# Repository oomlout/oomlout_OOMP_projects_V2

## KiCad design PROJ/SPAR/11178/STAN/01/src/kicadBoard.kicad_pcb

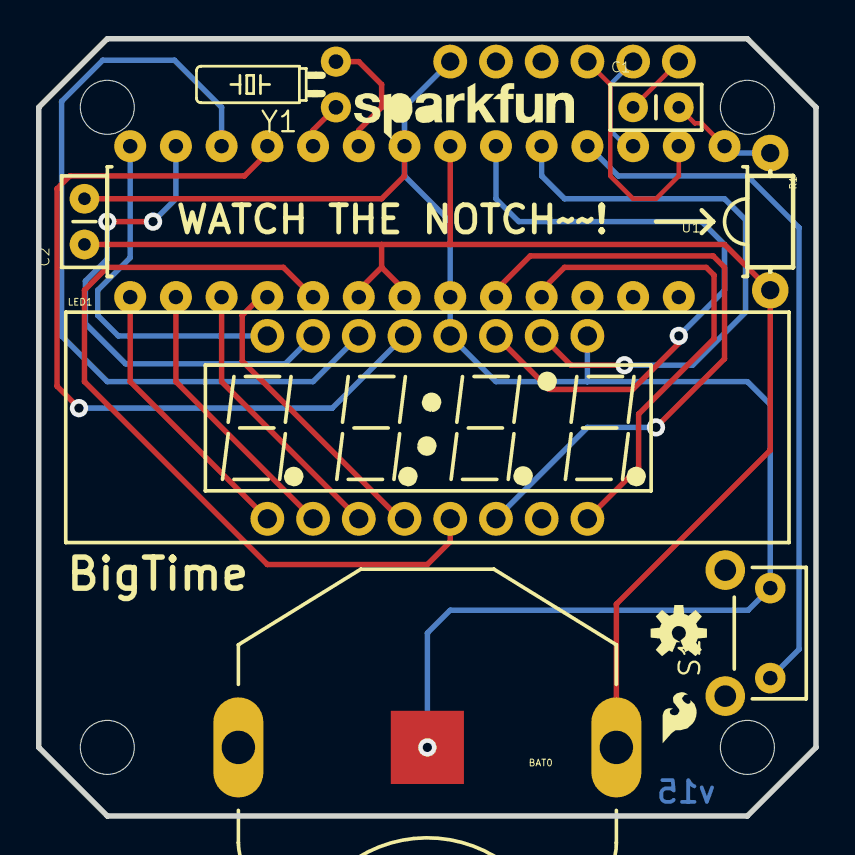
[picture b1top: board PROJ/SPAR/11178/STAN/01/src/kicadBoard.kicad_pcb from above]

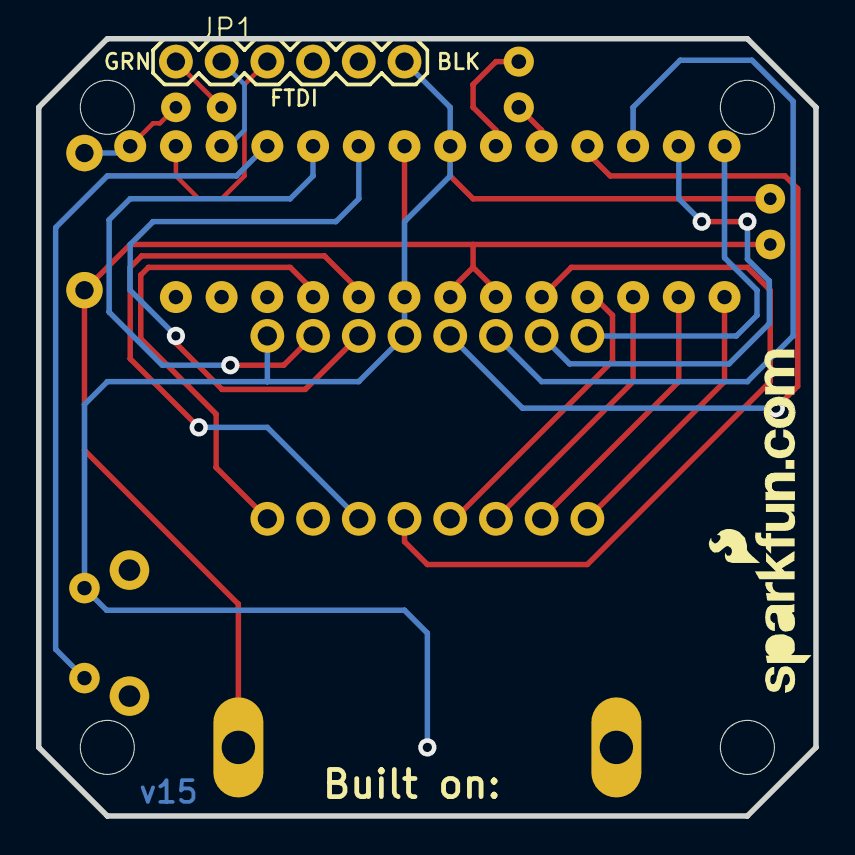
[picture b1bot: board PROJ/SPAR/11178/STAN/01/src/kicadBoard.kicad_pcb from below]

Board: 4 copper layers, 43.2 x 43.2 mm, 18 parts (2 on the bottom side), 22 nets.

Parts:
@HOLE0, @HOLE1, @HOLE2, @HOLE3: (no value)
BAT0: BATTERY_20MM_PTH_COMPACT
C1, C2: 100nF; CAP-PTH-SMALLEZ
JP1: FTDI_BASICPTH; FTDI_BASIC
LED1: 7-SEGMENT-4DIGIT-YOUNGSUNKIT; 7-SEGMENT-4DIGIT-YOUNGSUN-KIT
R1: 100k; AXIAL-0.3-KIT
S1: BUTTON; TACTILE-PTH-SIDEEZ
U1: ATMEGA328P_PDIP_EZ; DIL28-EZ
U$1: LOGO-SFESK; SFE-LOGO-FLAME
U$2: CREATIVE_COMMONS
U$3: LOGO-SFENEW; SFE-NEW-WEBLOGO
U$4: OSHW-LOGOS; OSHW-LOGO-S
U$5: LOGO-SFENW2; SFE-NEW-WEB
Y1: 32.768kHz; TC26HEZ

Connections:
A: LED1.14, U1.12
AMPM: LED1.10, U1.5
B: LED1.16, U1.14
BTN: S1.1, U1.4
C: LED1.13, U1.11
COL: LED1.4, U1.18
D: LED1.3, U1.17
DIG1: LED1.1, U1.15
DIG2: LED1.2, U1.16
DIG3: LED1.6, U1.23
DIG4: LED1.8, U1.24
E: LED1.5, U1.19
F: LED1.11, U1.6
G: LED1.15, U1.13
GND: BAT0.2, C2.2, JP1.GND, LED1.9, LED1.12, S1.2, U1.8, U1.22
unnamed: U1.10, Y1.1
unnamed: U1.9, Y1.2
unnamed: C1.1, JP1.DTR
RST: C1.2, R1.P$1, U1.1
RXI: JP1.TXO, U1.2
TXO: JP1.RXI, U1.3
VCC: BAT0.1, C2.1, R1.P$2, U1.7, U1.20, U1.21

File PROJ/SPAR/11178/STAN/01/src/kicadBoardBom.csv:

"Id";"Designator";"Package";"Quantity";"Designation";"Supplier and ref";
1;"U$1";"SFE-LOGO-FLAME";1;"LOGO-SFESK";;;
2;"U1";"DIL28-EZ";1;"ATMEGA328P_PDIP_EZ";;;
3;"@HOLE1,@HOLE2,@HOLE3,@HOLE0";"";4;"";;;
4;"C2,C1";"CAP-PTH-SMALLEZ";2;"100nF";;;
5;"Y1";"TC26HEZ";1;"32.768kHz";;;
6;"U$5";"SFE-NEW-WEB";1;"LOGO-SFENW2";;;
7;"R1";"AXIAL-0.3-KIT";1;"100k";;;
8;"U$4";"OSHW-LOGO-S";1;"OSHW-LOGOS";;;
9;"BAT0";"BATTERY_20MM_PTH_COMPACT";1;"";;;
10;"U$2";"CREATIVE_COMMONS";1;"CREATIVE_COMMONS";;;
11;"LED1";"7-SEGMENT-4DIGIT-YOUNGSUN-KIT";1;"7-SEGMENT-4DIGIT-YOUNGSUNKIT";;;
12;"S1";"TACTILE-PTH-SIDEEZ";1;"BUTTON";;;
13;"U$3";"SFE-NEW-WEBLOGO";1;"LOGO-SFENEW";;;
14;"JP1";"FTDI_BASIC";1;"FTDI_BASICPTH";;;

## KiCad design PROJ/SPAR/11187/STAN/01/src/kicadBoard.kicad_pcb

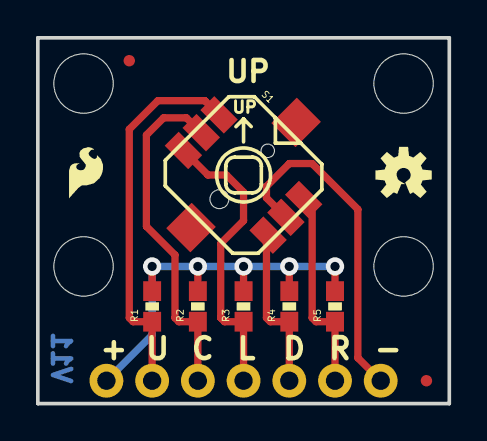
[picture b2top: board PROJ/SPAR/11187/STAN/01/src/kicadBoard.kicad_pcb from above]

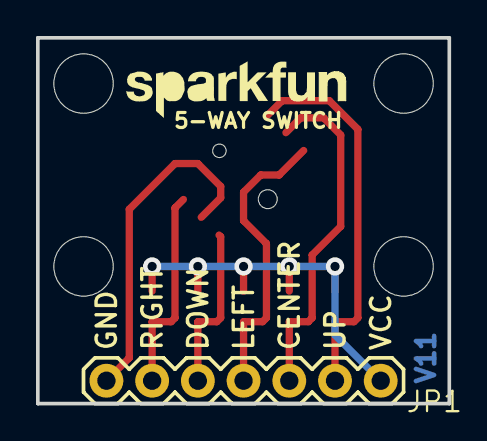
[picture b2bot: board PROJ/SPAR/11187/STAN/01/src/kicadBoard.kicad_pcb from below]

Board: 2 copper layers, 22.9 x 20.3 mm, 17 parts (2 on the bottom side), 7 nets.

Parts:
JP1: 1X07
JP2, JP7: FIDUCIALUFIDUCIAL; MICRO-FIDUCIAL
JP3, JP4, JP5, JP6: STAND-OFF
JP9: LOGO-SFESK; SFE-LOGO-FLAME
JP10: LOGO-SFENW2; SFE-NEW-WEB
R1, R2, R3, R4, R5: 10K; 0603-RES
S1: 5-WAY-TACTILE-SWITCH; JOYSTICK_MINI
U$1: OSHW-LOGOS; OSHW-LOGO-S
U$2: CREATIVE_COMMONS

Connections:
CENTER: JP1.3, R2.1, S1.CTR
DOWN: JP1.5, R4.1, S1.D
GND: JP1.7, S1.GND
LEFT: JP1.4, R3.1, S1.C
RIGHT: JP1.6, R5.1, S1.B
UP: JP1.2, R1.1, S1.A
VCC: JP1.1, R1.2, R2.2, R3.2, R4.2, R5.2

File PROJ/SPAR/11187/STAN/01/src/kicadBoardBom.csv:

"Id";"Designator";"Package";"Quantity";"Designation";"Supplier and ref";
1;"JP2,JP7";"MICRO-FIDUCIAL";2;"FIDUCIALUFIDUCIAL";;;
2;"JP6,JP5,JP3,JP4";"STAND-OFF";4;"STAND-OFF";;;
3;"S1";"JOYSTICK_MINI";1;"5-WAY-TACTILE-SWITCH";;;
4;"R3,R2,R1,R4,R5";"0603-RES";5;"10K";;;
5;"U$2";"CREATIVE_COMMONS";1;"CREATIVE_COMMONS";;;
6;"JP9";"SFE-LOGO-FLAME";1;"LOGO-SFESK";;;
7;"U$1";"OSHW-LOGO-S";1;"OSHW-LOGOS";;;
8;"JP1";"1X07";1;"";;;
9;"JP10";"SFE-NEW-WEB";1;"LOGO-SFENW2";;;

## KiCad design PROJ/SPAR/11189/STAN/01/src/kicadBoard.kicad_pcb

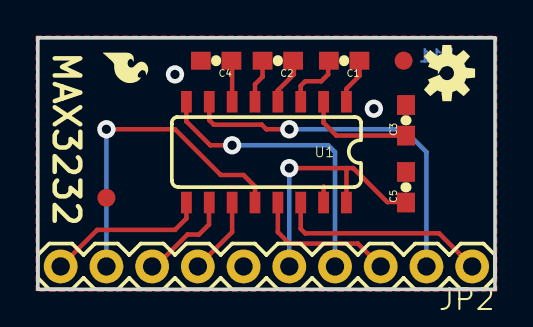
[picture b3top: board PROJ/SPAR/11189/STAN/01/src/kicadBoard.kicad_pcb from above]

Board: 2 copper layers, 25.4 x 14.0 mm, 12 parts (0 on the bottom side), 16 nets.

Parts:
C1, C2, C3, C4, C5: .1uF; 0603-CAP
FID1, FID2: FIDUCIAL1X2; FIDUCIAL-1X2
FRAME1: CREATIVE_COMMONS
JP2: M10"; 1X10
LOGO1: SFE_LOGO_FLAME.1_INCH; SFE_LOGO_FLAME_.1
U1: MAX3232; SO016
U$1: OSHW-LOGOS; OSHW-LOGO-S

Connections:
C1+: C1.1, U1.1
C1-: C1.2, U1.3
C2+: C2.1, U1.4
C2-: C2.2, U1.5
GND: C3.2, C4.2, C5.2, JP2.6, U1.15
R1IN: JP2.3, U1.13
R1OUT: JP2.9, U1.12
R2IN: JP2.4, U1.8
R2OUT: JP2.10, U1.9
T1IN: JP2.7, U1.11
T1OUT: JP2.1, U1.14
T2IN: JP2.8, U1.10
T2OUT: JP2.2, U1.7
V+: C3.1, U1.2
V-: C4.1, U1.6
VCC: C5.1, JP2.5, U1.16

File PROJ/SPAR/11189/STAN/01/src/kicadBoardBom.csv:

"Id";"Designator";"Package";"Quantity";"Designation";"Supplier and ref";
1;"C4,C2,C1,C3,C5";"0603-CAP";5;".1uF";;;
2;"U1";"SO016";1;"MAX3232";;;
3;"LOGO1";"SFE_LOGO_FLAME_.1";1;"SFE_LOGO_FLAME.1_INCH";;;
4;"U$1";"OSHW-LOGO-S";1;"OSHW-LOGOS";;;
5;"FRAME1";"CREATIVE_COMMONS";1;"";;;
6;"FID2,FID1";"FIDUCIAL-1X2";2;"FIDUCIAL1X2";;;
7;"JP2";"1X10";1;"M10"";;;

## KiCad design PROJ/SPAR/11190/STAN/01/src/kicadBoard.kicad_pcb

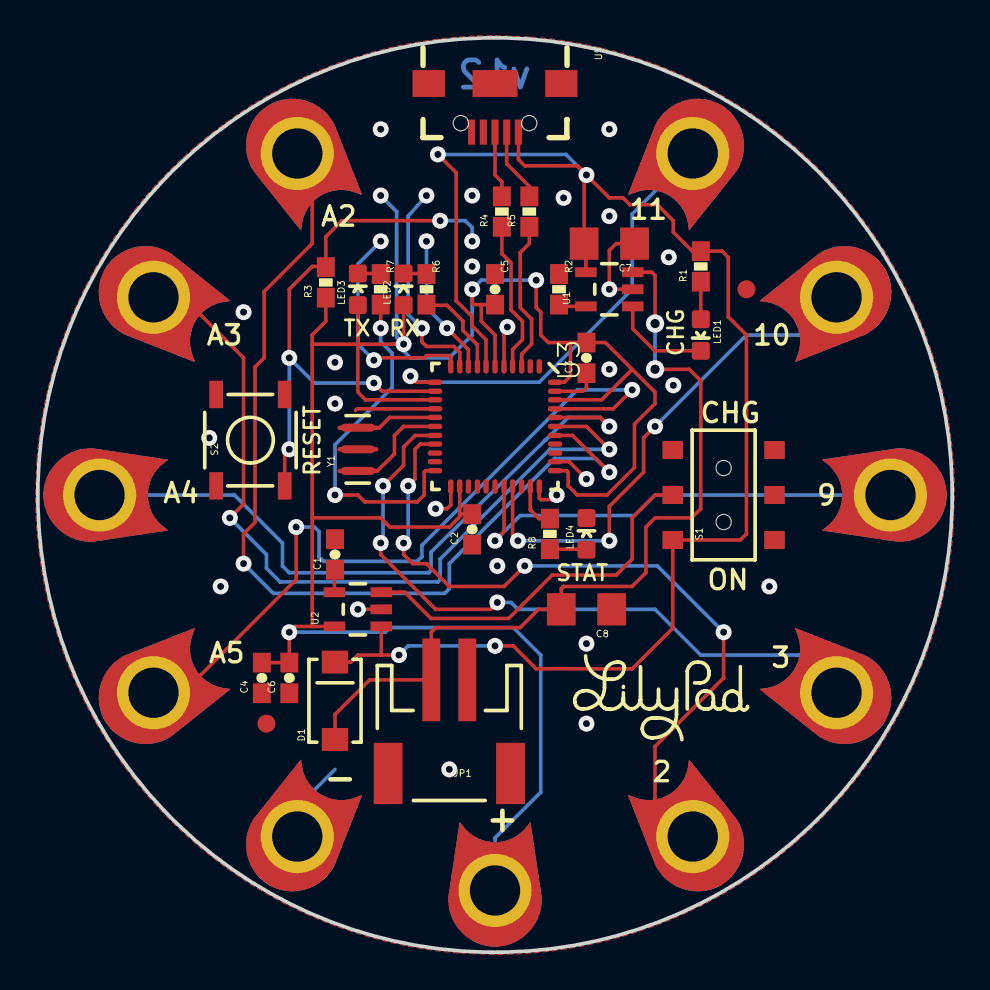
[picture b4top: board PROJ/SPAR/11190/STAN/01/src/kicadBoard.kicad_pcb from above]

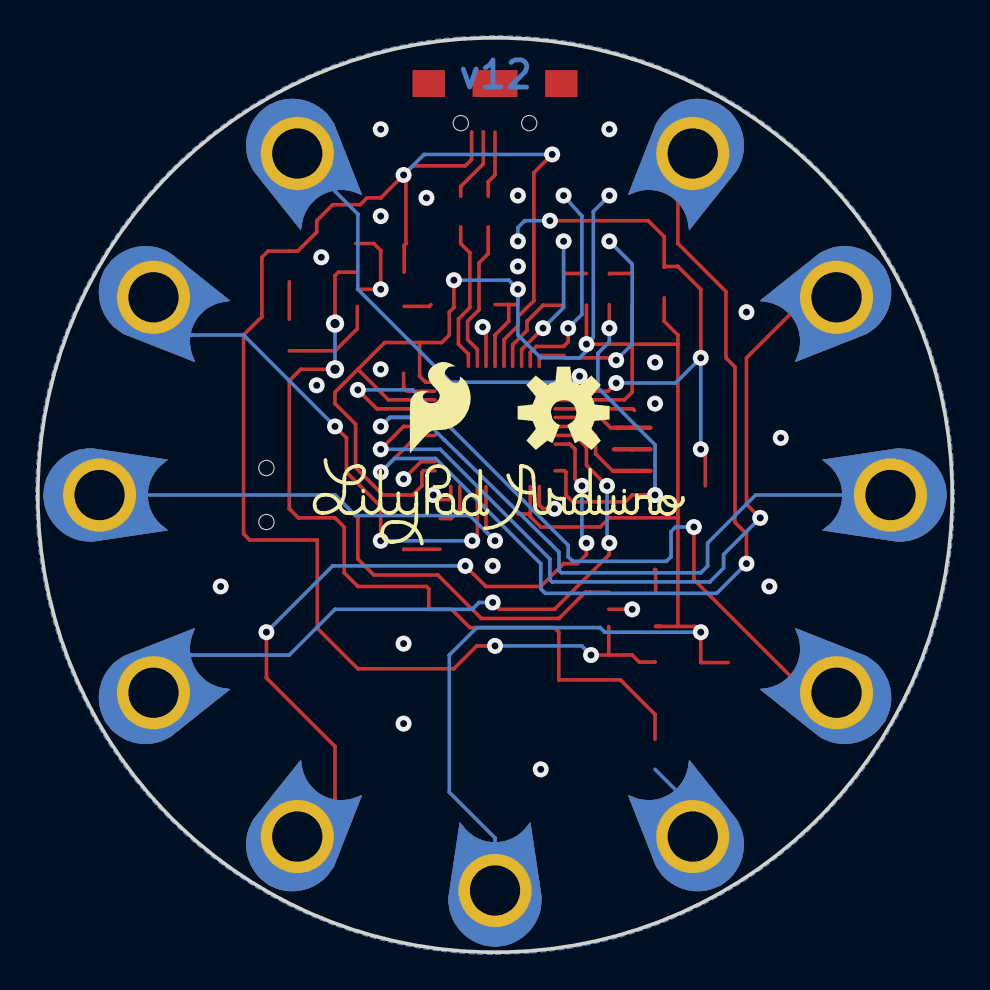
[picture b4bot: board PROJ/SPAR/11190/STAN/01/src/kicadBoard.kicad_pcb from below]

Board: 4 copper layers, 50.8 x 50.8 mm, 47 parts (3 on the bottom side), 31 nets.

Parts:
+0: SEWTAP9; PETAL-LONG-1-2SIDE
-0: SEWTAP9; PETAL-LONG-1-2SIDE
A2, A3, A4, A5: SEWTAP9; PETAL-LONG-1-2SIDE
C1: 470pF; 0603-CAP
C2, C3, C4: .1uF; 0603-CAP
C5: 1uF; 0603-CAP
C6: 4.7uF; 0603-CAP
C7, C8: 4.7uF; 1206
D1: B340A; SMA-DIODE
D5, D6, D9, D10, D11: SEWTAP9; PETAL-LONG-1-2SIDE
FRAME1: FRAME-LETTER; CREATIVE_COMMONS
JP1: JST-2; JST-2-SMD
JP2, JP3: FIDUCIAL1X2; FIDUCIAL-1X2
LED1, LED2, LED3, LED4: RED; LED-0603
R1, R6, R7, R8: 330; 0603-RES
R2, R3: 10k; 0603-RES
R4, R5: 22; 0603-RES
S1: AYZ0202
S2: !RESET; TACTILE_SWITCH_SMD
U1: MCP73831; SOT23-5
U2: MIC5219; SOT23-5
U3: ATMEGA32U41:1-LESS_PASTE; QFN-44-NOPAD_1_1-LESS_PASTE
U5: USB-AB-MICRO-SMD_V03
U$1: LOGO-LPLPA; LOGO-LPA
U$5: OSHW-LOGOM; OSHW-LOGO-M
U$7: SFE_LOGO_FLAME_.2
U$13: LOGO-LPLP; LOGO-LILYPAD
Y1: 8MHz; RESONATOR-SMD

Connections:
3.3V: +0.1, C2.2, C3.2, C4.2, C5.2, C6.2, LED2.A, LED3.A, R3.1, U2.5, U3.6, U3.14, U3.24, U3.34, U3.42, U3.44
5V: C7.2, D1.C, R1.2, S1.1, U1.4, U2.1, U3.7, U5.VBUS1
D+: R4.1, U3.4
D-: R5.1, U3.3
GND: -0.1, C1.2, C2.1, C3.1, C4.1, C5.1, C6.1, C7.1, C8.1, JP1.1, LED4.C, R2.1, S1.3, S2.1, U1.2, U2.2, U3.5, U3.15, U3.23, U3.33, U3.35, U3.43, U5.GND1, Y1.2
unnamed: LED2.C, R6.1
unnamed: S1.2, U2.3
unnamed: LED1.A, R1.1
unnamed: LED1.C, U1.1
unnamed: U3.17, Y1.1
unnamed: R2.2, U1.5
unnamed: U3.16, Y1.3
unnamed: C1.1, U2.4
unnamed: D11.1, U3.12
unnamed: D10.1, U3.30
unnamed: D9.1, U3.29
unnamed: D5.1, U3.19
unnamed: D6.1, U3.18
unnamed: A5.1, U3.41
unnamed: A4.1, U3.40
unnamed: A3.1, U3.39
unnamed: A2.1, U3.38
unnamed: LED4.A, R8.1
unnamed: R5.2, U5.D-1
unnamed: R4.2, U5.D+1
unnamed: LED3.C, R7.1
RESET: R3.2, S2.3, U3.13
RX_LED: R6.2, U3.8
TX_LED: R7.2, U3.22
USER_LED: R8.2, U3.32
V_BATT: C8.2, D1.A, JP1.2, U1.3

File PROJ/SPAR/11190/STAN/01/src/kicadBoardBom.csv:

"Id";"Designator";"Package";"Quantity";"Designation";"Supplier and ref";
1;"-0,D5,A2,D11,D9,A4,A5,D6,D10,A3,+0";"PETAL-LONG-1-2SIDE";11;"SEWTAP9";;;
2;"R8,R6,R7,R1";"0603-RES";4;"330";;;
3;"C8,C7";"1206";2;"4.7uF";;;
4;"S2";"TACTILE_SWITCH_SMD";1;"!RESET";;;
5;"C5";"0603-CAP";1;"1uF";;;
6;"Y1";"RESONATOR-SMD";1;"8MHz";;;
7;"R3,R2";"0603-RES";2;"10k";;;
8;"JP3,JP2";"FIDUCIAL-1X2";2;"FIDUCIAL1X2";;;
9;"LED3,LED2,LED4,LED1";"LED-0603";4;"RED";;;
10;"C4,C3,C2";"0603-CAP";3;".1uF";;;
11;"U$13";"LOGO-LILYPAD";1;"LOGO-LPLP";;;
12;"S1";"AYZ0202";1;"";;;
13;"JP1";"JST-2-SMD";1;"JST-2";;;
14;"FRAME1";"CREATIVE_COMMONS";1;"FRAME-LETTER";;;
15;"C6";"0603-CAP";1;"4.7uF";;;
16;"R5,R4";"0603-RES";2;"22";;;
17;"C1";"0603-CAP";1;"470pF";;;
18;"D1";"SMA-DIODE";1;"B340A";;;
19;"U2";"SOT23-5";1;"MIC5219";;;
20;"U1";"SOT23-5";1;"MCP73831";;;
21;"U3";"QFN-44-NOPAD_1_1-LESS_PASTE";1;"ATMEGA32U41:1-LESS_PASTE";;;
22;"U5";"USB-AB-MICRO-SMD_V03";1;"";;;
23;"U$5";"OSHW-LOGO-M";1;"OSHW-LOGOM";;;
24;"U$7";"SFE_LOGO_FLAME_.2";1;"";;;
25;"U$1";"LOGO-LPA";1;"LOGO-LPLPA";;;

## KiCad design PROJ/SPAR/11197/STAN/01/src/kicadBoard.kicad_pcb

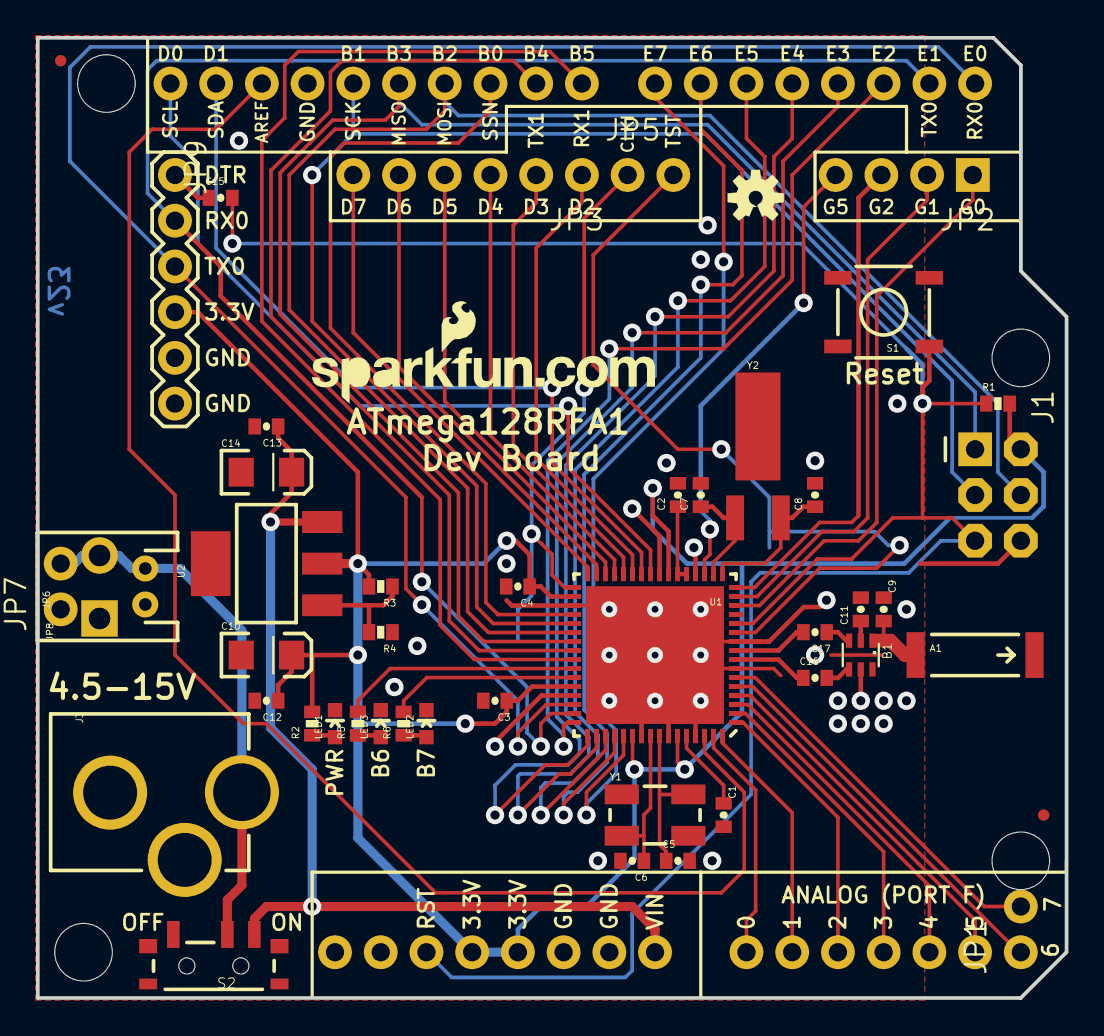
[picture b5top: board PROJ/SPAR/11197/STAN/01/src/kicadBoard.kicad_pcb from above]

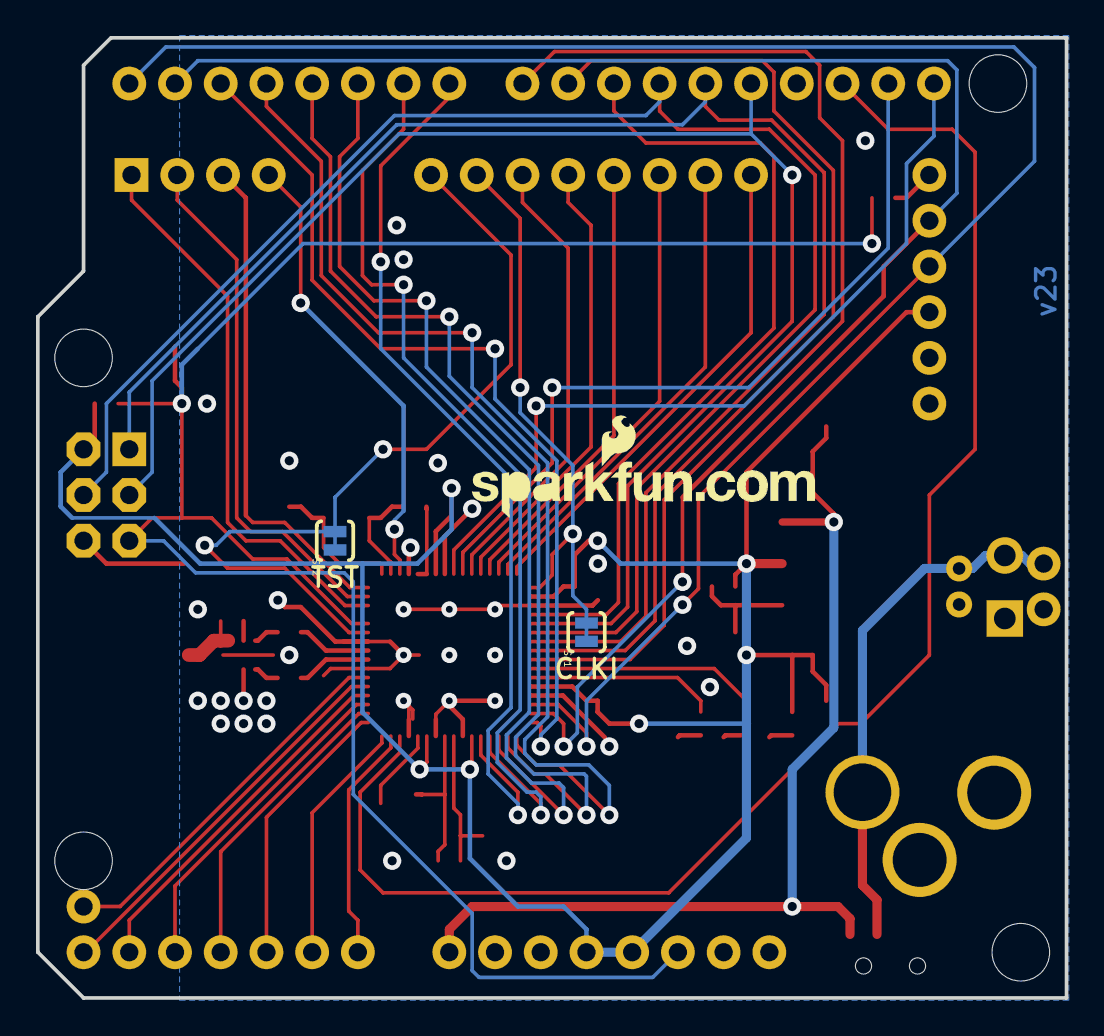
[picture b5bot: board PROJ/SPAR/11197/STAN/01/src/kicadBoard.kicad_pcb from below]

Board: 2 copper layers, 57.1 x 53.3 mm, 52 parts (3 on the bottom side), 61 nets.

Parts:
A1: ANTENNA2SMD5; ANTENNA-CHIP5
B1: 748421245; BALUN
C1, C2, C3, C4, C12: 1uF; 0402-CAP
C5, C6, C7, C8: 12pF; 0402-CAP
C9: 0.75pF; 0402-CAP
C10, C14: 10uF; EIA3216
C11: 22pF; 0402-CAP
C13, C15: 0.1uF; 0402-CAP
C16, C17: JUMP; 0402-CAP
FID1, FID2: FIDUCIALUFIDUCIAL; MICRO-FIDUCIAL
J1: ISP; 2X3-NS
J2: ARDUINO_UNO_R3
J3: POWER_JACKPTH_LOCK; POWER_JACK_PTH_LOCK
JP1, JP5, JP7: 1X02_NO_SILK
JP2: 1X04_NO_SILK
JP3: 1X06_NS
JP4, JP10: LOGO-SFENEW; SFE-NEW-WEBLOGO
JP6: JST-2-PTH
JP8: SCREWTERMINAL-3.5MM-2-NS
JP9: FTDI; FTDI_BASIC
LED1: RED; LED-0603
LED2, LED3: GREEN; LED-0603
R1: 10k; 0402-RES
R2: 1k; 0402-RES
R3: 240; 0402-RES
R4: 390; 0402-RES
R5, R6: 330; 0402-RES
S1: TACTILE_SWITCH_SMD
S2: SWITCH-SPST-SMD-A
SJ1, SJ2: SJ_2S-TRACE
U1: ATMEGA128RFA1; QFN-64
U2: LM1117; SOT223
U$1: OSHW-LOGOS; OSHW-LOGO-S
Y1: 16MHz; CRYSTAL-SMD-5X3
Y2: 32.768kHz; CRYSTAL-32KHZ-SMD

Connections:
3.3V: C3.1, C4.1, C10.A, C12.1, J1.2, J2.3.3V, J2.5V, JP9.VCC, R1.2, R2.2, R3.2, U1.23, U1.34, U1.44, U1.54, U1.59, U2.2
A0: J2.A0, U1.63
A1: J2.A1, U1.64
A2: J2.A2, U1.1
A3: J2.A3, U1.2
A4: J2.A4, U1.3
A5: J2.A5, U1.4
A6: JP1.1, U1.5
A7: JP1.2, U1.6
AREF: J2.AREF, U1.62
AVDD: C1.1, U1.60
CLKI: JP5.1, SJ1.2, U1.33
DTR: C15.1, JP9.DTR
DVDD: C2.1, U1.21, U1.22
FB: R3.1, R4.2, U2.1
GND: B1.5, C1.2, C2.2, C3.2, C4.2, C5.2, C6.2, C7.2, C8.2, C9.1, C10.C, C11.2, C12.2, C13.2, C14.C, J1.6, J2.GND@0, J2.GND@1, J2.GND@2, J3.GND, J3.GNDBREAK, JP6.1, JP7.1, JP8.1, JP9.GND, LED1.C, LED2.C, LED3.C, R4.1, S1.3, SJ1.1, SJ2.1, U1.7, U1.10, U1.20, U1.24, U1.35, U1.45, U1.55, U1.58, U1.61, U1.65
MISO: J1.1, J2.D12, U1.39
MOSI: J1.4, J2.D11, U1.38
unnamed: LED1.A, R2.1
unnamed: C5.1, U1.57, Y1.3
unnamed: C6.1, U1.56, Y1.1
unnamed: C7.1, U1.18, Y2.X1
unnamed: C8.1, U1.17, Y2.X2
unnamed: B1.2, C11.1
unnamed: LED3.A, R5.1
unnamed: J3.PWR, JP6.2, JP7.2, JP8.2, S2.2
unnamed: B1.4, C16.2
unnamed: B1.3, C17.1
unnamed: LED2.A, R6.1
PB4: J2.D9, U1.40
PB5: J2.D8, U1.41
PB6: R5.2, U1.42
PB7: R6.2, U1.43
PD4: JP3.3, U1.29
PD5: JP3.4, U1.30
PD6: JP3.5, U1.31
PD7: JP3.6, U1.32
PE2: J2.D2, U1.48
PE3: J2.D3, U1.49
PE4: J2.D4, U1.50
PE5: J2.D5, U1.51
PE6: J2.D6, U1.52
PE7: J2.D7, U1.53
PG0: JP2.1, U1.14
PG1: JP2.2, U1.15
PG2: JP2.3, U1.16
PG5: JP2.4, U1.19
RESET: C15.2, J1.5, J2.RES, R1.1, S1.1, U1.12
RFANT: A1.FEED, B1.1, C9.2
RFN: C17.2, U1.9
RFP: C16.1, U1.8
RX0: J2.RX, JP9.TXO, U1.46
RX1: JP3.1, U1.27
SCK: J1.3, J2.D13, U1.37
SCL: J2.SCL, U1.25
SDA: J2.SDA, U1.26
SSN: J2.D10, U1.36
TST: JP5.2, SJ2.2, U1.11
TX0: J2.TX, JP9.RXI, U1.47
TX1: JP3.2, U1.28
VCC: C13.1, C14.A, J2.VIN, S2.1, U2.3

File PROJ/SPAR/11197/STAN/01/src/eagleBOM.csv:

"Part";"Value";"Device";"Package";"Description";"";
"A1";"ANTENNA2SMD5";"ANTENNA2SMD5";"ANTENNA-CHIP5";"Chip antenna";"";
"B1";"748421245";"BALUN0805";"BALUN";"0805 footprint balun- Ember 351/357";"";
"C1";"1uF";"CAP0402-CAP";"0402-CAP";"Capacitor";"";
"C2";"1uF";"CAP0402-CAP";"0402-CAP";"Capacitor";"";
"C3";"1uF";"CAP0402-CAP";"0402-CAP";"Capacitor";"";
"C4";"1uF";"CAP0402-CAP";"0402-CAP";"Capacitor";"";
"C5";"12pF";"CAP0402-CAP";"0402-CAP";"Capacitor";"";
"C6";"12pF";"CAP0402-CAP";"0402-CAP";"Capacitor";"";
"C7";"12pF";"CAP0402-CAP";"0402-CAP";"Capacitor";"";
"C8";"12pF";"CAP0402-CAP";"0402-CAP";"Capacitor";"";
"C9";"0.75pF";"CAP0402-CAP";"0402-CAP";"Capacitor";"";
"C10";"10uF";"CAP_POL1206";"EIA3216";"Capacitor Polarized";"";
"C11";"22pF";"CAP0402-CAP";"0402-CAP";"Capacitor";"";
"C12";"1uF";"CAP0402-CAP";"0402-CAP";"Capacitor";"";
"C13";"0.1uF";"CAP0402-CAP";"0402-CAP";"Capacitor";"";
"C14";"10uF";"CAP_POL1206";"EIA3216";"Capacitor Polarized";"";
"C15";"0.1uF";"CAP0402-CAP";"0402-CAP";"Capacitor";"";
"C16";"JUMP";"CAP0402-CAP";"0402-CAP";"Capacitor";"";
"C17";"JUMP";"CAP0402-CAP";"0402-CAP";"Capacitor";"";
"FID1";"FIDUCIALUFIDUCIAL";"FIDUCIALUFIDUCIAL";"MICRO-FIDUCIAL";"Fiducial Alignment Points";"";
"FID2";"FIDUCIALUFIDUCIAL";"FIDUCIALUFIDUCIAL";"MICRO-FIDUCIAL";"Fiducial Alignment Points";"";
"J1";"ISP";"AVR_SPI_PRG_6NS";"2X3-NS";"AVR ISP 6 Pin";"";
"J2";"ARDUINO_UNO_R3";"ARDUINO_UNO_R3";"ARDUINO_UNO_R3";"Arduino Uno R3";"";
"J3";"POWER_JACKPTH_LOCK";"POWER_JACKPTH_LOCK";"POWER_JACK_PTH_LOCK";"Power Jack";"";
"JP1";"";"M021X02_NO_SILK";"1X02_NO_SILK";"Header 2";"";
"JP2";"";"M041X04_NO_SILK";"1X04_NO_SILK";"Header 4";"";
"JP3";"";"M06SIP-NS";"1X06_NS";"Header 6";"";
"JP4";"LOGO-SFENEW";"LOGO-SFENEW";"SFE-NEW-WEBLOGO";"Spark Fun Electronics PCB Logo";"";
"JP5";"";"M021X02_NO_SILK";"1X02_NO_SILK";"Header 2";"";
"JP6";"";"M02JST-PTH-2";"JST-2-PTH";"Header 2";"";
"JP7";"";"M021X02_NO_SILK";"1X02_NO_SILK";"Header 2";"";
"JP8";"";"M023.5MM-NO_SILK";"SCREWTERMINAL-3.5MM-2-NS";"Header 2";"";
"JP9";"FTDI";"FTDI_BASICPTH";"FTDI_BASIC";"FTDI Basic header with labels";"";
"JP10";"LOGO-SFENEW";"LOGO-SFENEW";"SFE-NEW-WEBLOGO";"Spark Fun Electronics PCB Logo";"";
"LED1";"RED";"LED0603";"LED-0603";"LEDs";"";
"LED2";"GREEN";"LED0603";"LED-0603";"LEDs";"";
"LED3";"GREEN";"LED0603";"LED-0603";"LEDs";"";
"R1";"10k";"RESISTOR0402-RES";"0402-RES";"Resistor";"";
"R2";"1k";"RESISTOR0402-RES";"0402-RES";"Resistor";"";
"R3";"240";"RESISTOR0402-RES";"0402-RES";"Resistor";"";
"R4";"390";"RESISTOR0402-RES";"0402-RES";"Resistor";"";
"R5";"330";"RESISTOR0402-RES";"0402-RES";"Resistor";"";
"R6";"330";"RESISTOR0402-RES";"0402-RES";"Resistor";"";
"S1";"";"SWITCH-MOMENTARY-2SMD";"TACTILE_SWITCH_SMD";"Various NO switches- pushbuttons, reed, etc";"";
"S2";"";"SWITCH-SPST-SMD-A";"SWITCH-SPST-SMD-A";"SPST Switch";"";
"SJ1";"";"SOLDERJUMPERTRACE";"SJ_2S-TRACE";"Solder Jumper";"";
"SJ2";"";"SOLDERJUMPERTRACE";"SJ_2S-TRACE";"Solder Jumper";"";
"U$1";"OSHW-LOGOS";"OSHW-LOGOS";"OSHW-LOGO-S";"Open Source Hardware Logo This logo indicates the piece of hardware it is found on incorporates a OSHW license and/or adheres to the definition of open source hardware found here: http://freedomdefined.org/OSHW";"";
"U1";"ATMEGA128RFA1";"ATMEGA128RFA1";"QFN-64";"ATmega128RFA1";"";
"U2";"LM1117";"V_REG_317SMD";"SOT223";"Voltage Regulator";"";
"Y1";"16MHz";"CRYSTAL5X3";"CRYSTAL-SMD-5X3";"Various standard crystals. Proven footprints. Spark Fun Electronics SKU : COM-00534";"";
"Y2";"32.768kHz";"CRYSTAL32-SMD";"CRYSTAL-32KHZ-SMD";"Various standard crystals. Proven footprints. Spark Fun Electronics SKU : COM-00534";"";

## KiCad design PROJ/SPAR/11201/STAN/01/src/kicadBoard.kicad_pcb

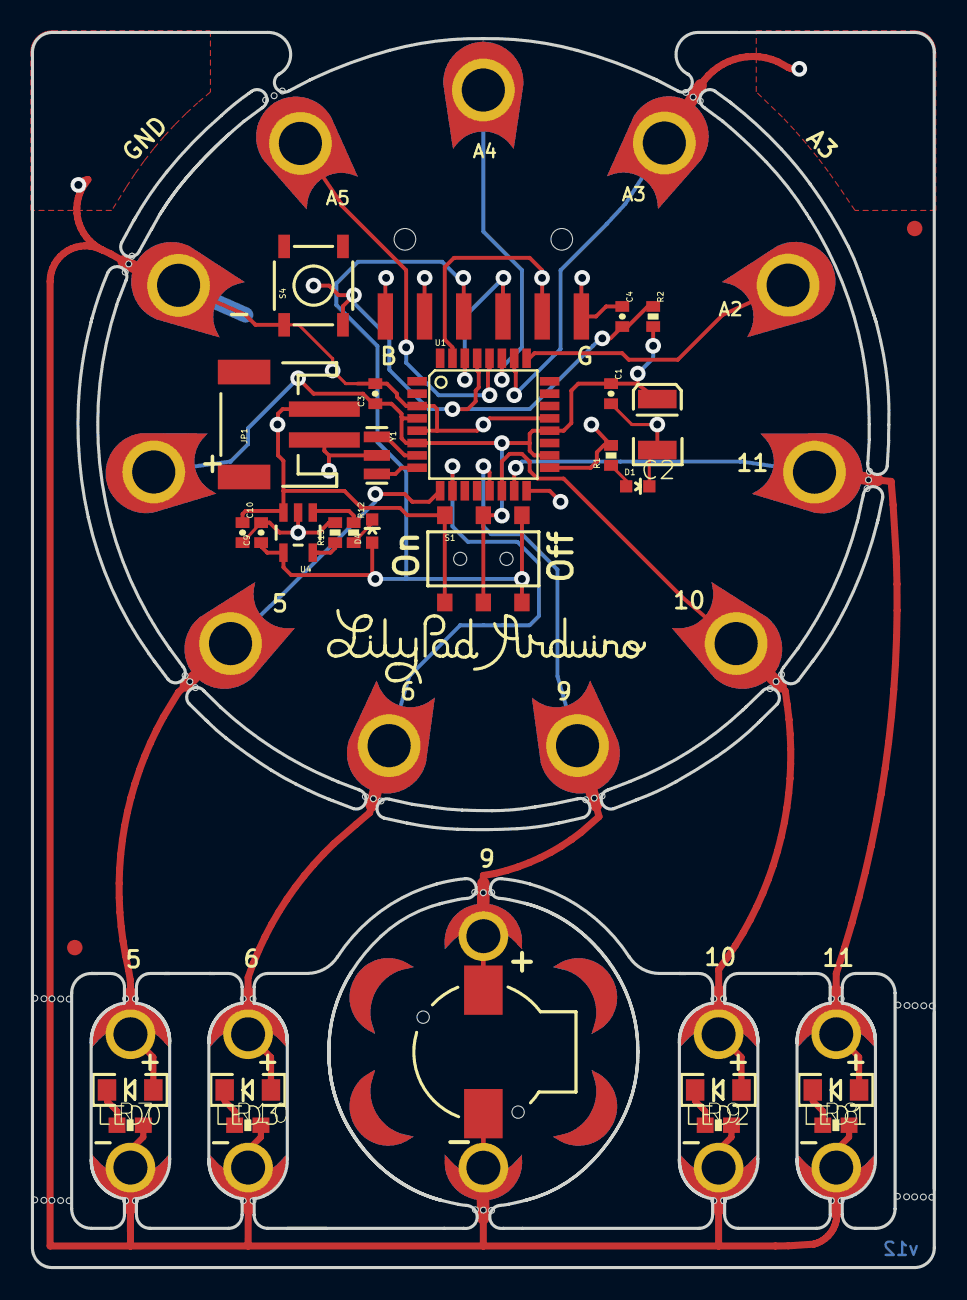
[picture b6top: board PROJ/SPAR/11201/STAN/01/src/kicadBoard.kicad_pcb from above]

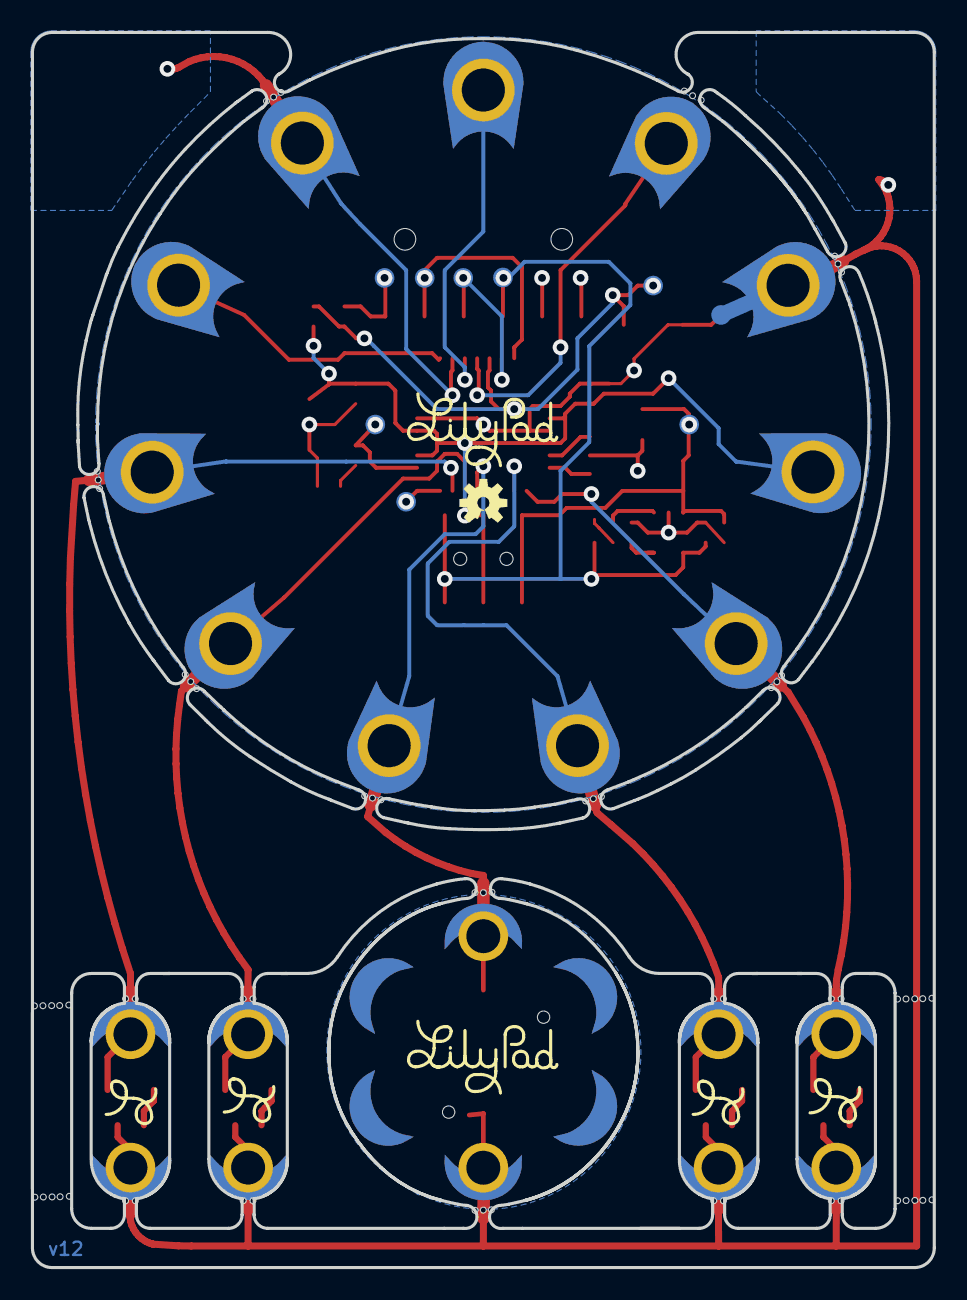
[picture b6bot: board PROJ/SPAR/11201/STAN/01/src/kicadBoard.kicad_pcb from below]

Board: 2 copper layers, 58.4 x 80.0 mm, 139 parts (16 on the bottom side), 29 nets.

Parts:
@HOLE0, @HOLE1, @HOLE2, @HOLE3, @HOLE4, @HOLE5, @HOLE6, @HOLE7, @HOLE8, @HOLE9, @HOLE10, @HOLE11, @HOLE12, @HOLE13, @HOLE14, @HOLE15, @HOLE16, @HOLE17, @HOLE18, @HOLE19, @HOLE20, @HOLE21, @HOLE22, @HOLE23, @HOLE24, @HOLE25, @HOLE26, @HOLE27, @HOLE28, @HOLE29, @HOLE30, @HOLE31, @HOLE32, @HOLE33, @HOLE34, @HOLE35, @HOLE36, @HOLE37, @HOLE38, @HOLE39, @HOLE40, @HOLE41, @HOLE42, @HOLE43, @HOLE44, @HOLE45, @HOLE46, @HOLE47, @HOLE48, @HOLE49, @HOLE50, @HOLE51, @HOLE52, @HOLE53, @HOLE54, @HOLE55, @HOLE56, @HOLE57, @HOLE58, @HOLE59, @HOLE60, @HOLE61, @HOLE62, @HOLE63, @HOLE64, @HOLE65: (no value)
A2/16, A3/17, A4/18, A5/19: SEWTAP9; PETAL-LONG-1-2SIDE
B1: Buzzer; BUZZER-CCV
C1, C4: 0.1uF; 0402-CAP
C2: 47uF; EIA3528
C3: 1.0uF; 0402-CAP
C9, C10: 4.7uF; 0402-CAP
D1: Status; LED-0603
D4: Yellow; LED-0603
JP1: LiPo; JST-2-SMD
JP2: 1X06-SMD
JP3, JP4: FIDUCIAL1X2; FIDUCIAL-1X2
LED0, LED1, LED2, LED3: White; LED-1206
LED+0, LED+1, LED+2, LED+3: SEWTAP6; PETAL-SMALL-2SIDE
LED-0, LED-1, LED-2, LED-3: SEWTAP6; PETAL-SMALL-2SIDE
LOGO0: LOGO-LPLPA; LOGO-LPA
LOGO3, LOGO4, LOGO5, LOGO6: LOGO-LPL; LOGO-L
PP-GND0: PAD.03X.05
PP-MISO0: PAD.03X.05
PP-RST0: PAD.03X.05
PP-SCK0: PAD.03X.05
R1, R12: 330; 0402-RES
R2: 10K; 0402-RES
R7, R8, R9, R10: 100; 0603-RES
R13: 10k; 0402-RES
S1: On/Off; AYZ0202
S4: Reset; TACTILE_SWITCH_SMD
TP1, TP2: PAD.03X.05
TP-DTR0: PAD.03X.05
TP-RX0: PAD.03X.05
TP-TX0: PAD.03X.05
U1: ATMEGA328; TQFP32-08
U4: MCP73831; SOT23-5
U$1, U$4, U$37, U$39, U$41, U$43, U$45: SEWTAP9; PETAL-LONG-1-2SIDE
U$2: OSHW-LOGOS; OSHW-LOGO-S
U$21, U$35: LOGO-LPLP; LOGO-LILYPAD
U$32-0, U$33+0: SEWTAP6; PETAL-SMALL-2SIDE
U$36: LILYPAD-BRD-LAYERS-SMALL
UNK1, UNK2, UNK3, UNK4: SEWTAP-NOHOLE2; PETAL-NOHOLE-2SIDE
Y1: 8MHz; RESONATOR-SMD

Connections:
A2: A2/16.1, U1.25
A3: A3/17.1, U1.26
A4: A4/18.1, U1.27
A5: A5/19.1, U1.28
D5: LED0.A, LED+0.1, U1.9, U$41.1
D6: LED3.A, LED+3.1, U1.10, U$1.1
D9: B1.+, U1.13, U$33+0.1, U$37.1
D10: LED2.A, LED+2.1, U1.14, U$39.1
D11: LED1.A, LED+1.1, U1.15, U$4.1
D12: PP-MISO0.P$1, U1.16
D13: PP-SCK0.P$1, R1.2, U1.17
DTR: C4.1, JP2.1, TP-DTR0.P$1
FTDI_VCC: C9.1, D4.A, JP2.4, S1.3, S1.6, TP1.P$1, U4.4
GND: B1.-, C1.2, C2.C, C3.2, C9.2, C10.2, D1.C, JP1.1, JP2.5, JP2.6, LED-0.1, LED-1.1, LED-2.1, LED-3.1, PP-GND0.P$1, R7.2, R8.2, R9.2, R10.2, R13.2, S4.1, U1.3, U1.5, U1.21, U4.2, U$32-0.1, U$43.1, Y1.2
unnamed: U1.7, Y1.1
unnamed: D1.A, R1.1
unnamed: U1.8, Y1.3
unnamed: LED0.C, R7.1
unnamed: LED1.C, R8.1
unnamed: LED2.C, R9.1
unnamed: LED3.C, R10.1
unnamed: D4.C, R12.2
PROG: R13.1, U4.5
RST: C4.2, PP-RST0.P$1, R2.1, S4.3, U1.29
RXI: JP2.3, TP-RX0.P$1, U1.30
STAT: R12.1, U4.1
TXO: JP2.2, TP-TX0.P$1, U1.31
VBATT: C10.1, JP1.2, S1.1, S1.4, TP2.P$1, U4.3
VCC: C1.1, C2.A, C3.1, R2.2, S1.2, S1.5, U1.4, U1.6, U1.18, U1.20, U$45.1

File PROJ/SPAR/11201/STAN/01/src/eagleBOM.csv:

"Part";"Value";"Device";"Package";"Description";"";
"1";"SEWTAP-NOHOLE2";"SEWTAP-NOHOLE2";"PETAL-NOHOLE-2SIDE";"";"";
"2";"SEWTAP-NOHOLE2";"SEWTAP-NOHOLE2";"PETAL-NOHOLE-2SIDE";"";"";
"3";"SEWTAP-NOHOLE2";"SEWTAP-NOHOLE2";"PETAL-NOHOLE-2SIDE";"";"";
"4";"SEWTAP-NOHOLE2";"SEWTAP-NOHOLE2";"PETAL-NOHOLE-2SIDE";"";"";
"A2/16";"SEWTAP9";"SEWTAP9";"PETAL-LONG-1-2SIDE";"";"";
"A3/17";"SEWTAP9";"SEWTAP9";"PETAL-LONG-1-2SIDE";"";"";
"A4/18";"SEWTAP9";"SEWTAP9";"PETAL-LONG-1-2SIDE";"";"";
"A5/19";"SEWTAP9";"SEWTAP9";"PETAL-LONG-1-2SIDE";"";"";
"B1";"Buzzer";"BUZZERSMD2";"BUZZER-CCV";"Buzzer 12mm";"";
"C1";"0.1uF";"CAP0402-CAP";"0402-CAP";"Capacitor";"";
"C2";"47uF";"CAP_POL3528";"EIA3528";"Capacitor Polarized";"";
"C3";"1.0uF";"CAP0402-CAP";"0402-CAP";"Capacitor";"";
"C4";"0.1uF";"CAP0402-CAP";"0402-CAP";"Capacitor";"";
"C9";"4.7uF";"CAP0402-CAP";"0402-CAP";"Capacitor";"";
"C10";"4.7uF";"CAP0402-CAP";"0402-CAP";"Capacitor";"";
"D1";"Status";"LED0603";"LED-0603";"LEDs";"";
"D4";"Yellow";"LED0603";"LED-0603";"LEDs";"";
"JP1";"LiPo";"M02-JST-2MM-SMT";"JST-2-SMD";"Header 2";"";
"JP2";"";"ARDUINO_SERIAL_PROGRAMSMD";"1X06-SMD";"";"";
"JP3";"FIDUCIAL1X2";"FIDUCIAL1X2";"FIDUCIAL-1X2";"Fiducial Alignment Points";"";
"JP4";"FIDUCIAL1X2";"FIDUCIAL1X2";"FIDUCIAL-1X2";"Fiducial Alignment Points";"";
"LED";"White";"LED1206";"LED-1206";"LEDs";"";
"LED+";"SEWTAP6";"SEWTAP6";"PETAL-SMALL-2SIDE";"";"";
"LED+1";"SEWTAP6";"SEWTAP6";"PETAL-SMALL-2SIDE";"";"";
"LED+2";"SEWTAP6";"SEWTAP6";"PETAL-SMALL-2SIDE";"";"";
"LED+3";"SEWTAP6";"SEWTAP6";"PETAL-SMALL-2SIDE";"";"";
"LED-";"SEWTAP6";"SEWTAP6";"PETAL-SMALL-2SIDE";"";"";
"LED-1";"SEWTAP6";"SEWTAP6";"PETAL-SMALL-2SIDE";"";"";
"LED-2";"SEWTAP6";"SEWTAP6";"PETAL-SMALL-2SIDE";"";"";
"LED-3";"SEWTAP6";"SEWTAP6";"PETAL-SMALL-2SIDE";"";"";
"LED1";"White";"LED1206";"LED-1206";"LEDs";"";
"LED2";"White";"LED1206";"LED-1206";"LEDs";"";
"LED3";"White";"LED1206";"LED-1206";"LEDs";"";
"LOGO";"LOGO-LPLPA";"LOGO-LPLPA";"LOGO-LPA";"";"";
"PP-GND";"";"TEST-POINT3X5";"PAD.03X.05";"";"";
"PP-MISO";"";"TEST-POINT3X5";"PAD.03X.05";"";"";
"PP-RST";"";"TEST-POINT3X5";"PAD.03X.05";"";"";
"PP-SCK";"";"TEST-POINT3X5";"PAD.03X.05";"";"";
"R1";"330";"RESISTOR0402-RES";"0402-RES";"Resistor";"";
"R2";"10K";"RESISTOR0402-RES";"0402-RES";"Resistor";"";
"R7";"100";"RESISTOR0603-RES";"0603-RES";"Resistor";"";
"R8";"100";"RESISTOR0603-RES";"0603-RES";"Resistor";"";
"R9";"100";"RESISTOR0603-RES";"0603-RES";"Resistor";"";
"R10";"100";"RESISTOR0603-RES";"0603-RES";"Resistor";"";
"R12";"330";"RESISTOR0402-RES";"0402-RES";"Resistor";"";
"R13";"10k";"RESISTOR0402-RES";"0402-RES";"Resistor";"";
"S1";"On/Off";"AYZ0202";"AYZ0202";"SPDT Slide Switch";"";
"S4";"Reset";"SWITCH-MOMENTARY-2SMD";"TACTILE_SWITCH_SMD";"";"";
"TP-DTR";"";"TEST-POINT3X5";"PAD.03X.05";"";"";
"TP-RX";"";"TEST-POINT3X5";"PAD.03X.05";"";"";
"TP-TX";"";"TEST-POINT3X5";"PAD.03X.05";"";"";
"TP1";"";"TEST-POINT3X5";"PAD.03X.05";"";"";
"TP2";"";"TEST-POINT3X5";"PAD.03X.05";"";"";
"U$1";"SEWTAP9";"SEWTAP9";"PETAL-LONG-1-2SIDE";"";"";
"U$2";"OSHW-LOGOS";"OSHW-LOGOS";"OSHW-LOGO-S";"Open Source Hardware Logo This logo indicates the piece of hardware it is found on incorporates a OSHW license and/or adheres to the definition of open source hardware found here: http://freedomdefined.org/OSHW";"";
"U$4";"SEWTAP9";"SEWTAP9";"PETAL-LONG-1-2SIDE";"";"";
"U$32-";"SEWTAP6";"SEWTAP4";"PETAL-SMALL";"";"";
"U$33+";"SEWTAP6";"SEWTAP4";"PETAL-SMALL";"";"";
"U$37";"SEWTAP9";"SEWTAP9";"PETAL-LONG-1-2SIDE";"";"";
"U$39";"SEWTAP9";"SEWTAP9";"PETAL-LONG-1-2SIDE";"";"";
"U$41";"SEWTAP9";"SEWTAP9";"PETAL-LONG-1-2SIDE";"";"";
"U$43";"SEWTAP9";"SEWTAP9";"PETAL-LONG-1-2SIDE";"";"";
"U$45";"SEWTAP9";"SEWTAP9";"PETAL-LONG-1-2SIDE";"";"";
"U1";"ATMEGA328";"ATMEGA168";"TQFP32-08";"";"";
"U4";"MCP73831";"MCP73831";"SOT23-5";"Microchip's MCP73831";"";
"Y1";"8MHz";"RESONATORSMD";"RESONATOR-SMD";"Resonator";"";

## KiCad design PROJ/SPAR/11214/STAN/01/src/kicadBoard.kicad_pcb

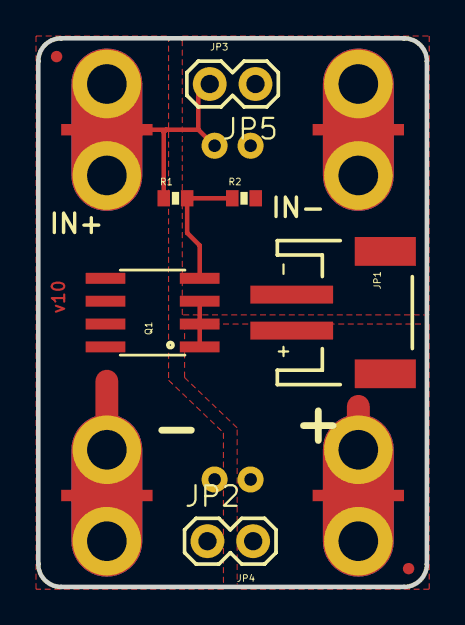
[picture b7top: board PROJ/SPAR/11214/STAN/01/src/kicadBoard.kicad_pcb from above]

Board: 4 copper layers, 21.6 x 30.5 mm, 15 parts (0 on the bottom side), 5 nets.

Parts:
BH1: TRIG+; BUTTONHOLE
BH2: TRIG-; BUTTONHOLE
BH3: OUT+; BUTTONHOLE
BH4: OUT-; BUTTONHOLE
FRAME1: FRAME-LETTER; CREATIVE_COMMONS
JP1: JST-SMT; JST-2-SMD
JP2, JP5: 1X02
JP3, JP4: JST-PTH; JST-2-PTH-NS
JP6, JP7: FIDUCIALUFIDUCIAL; MICRO-FIDUCIAL
Q1: FDS6630A; SO08
R1: 10k; 0402-RES
R2: 1M; 0402-RES

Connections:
GND: BH2.P$1, JP1.1, JP3.2, JP5.1, Q1.1, Q1.2, Q1.3, R2.2
unnamed: Q1.4, R1.2, R2.1
OUT-: BH4.P$1, JP2.1, JP4.2, Q1.5, Q1.6, Q1.7, Q1.8
TRIG+: BH1.P$1, JP3.1, JP5.2, R1.1
V_BATT: BH3.P$1, JP1.2, JP2.2, JP4.1

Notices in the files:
PROJ/SPAR/11201/STAN/01/src/kicadBoard.kicad_pcb:
Released under the Creative Commons Attribution Share-Alike 3.0 License
http://creativecommons.org/licenses/by-sa/3.0
parts and their libraries:
RELEASED UNDER THE CREATIVE COMMONS ATTRIBUTION SHARE-ALIKE 4.0 LICENSE
HTTPS://CREATIVECOMMONS.ORG/LICENSES/BY-SA/4.0
